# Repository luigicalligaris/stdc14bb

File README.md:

# stdc14bb
A STDC14 breakout board to 100-mil headers, one pair of 100-mil headers being one-to-one to the STDC14 and one being in a single line with additional pins for 3.3V power injection. Licensed under CERN Open Hardware Licence Version 2 - Strongly Reciprocal, see file LICENSE_cern_ohl_s_v2.txt for the full license content.

This board has been designed in KiCAD 7.0.6, a Free and Open Source EDA Software. See the KiCAD site for documentation: https://www.kicad.org/

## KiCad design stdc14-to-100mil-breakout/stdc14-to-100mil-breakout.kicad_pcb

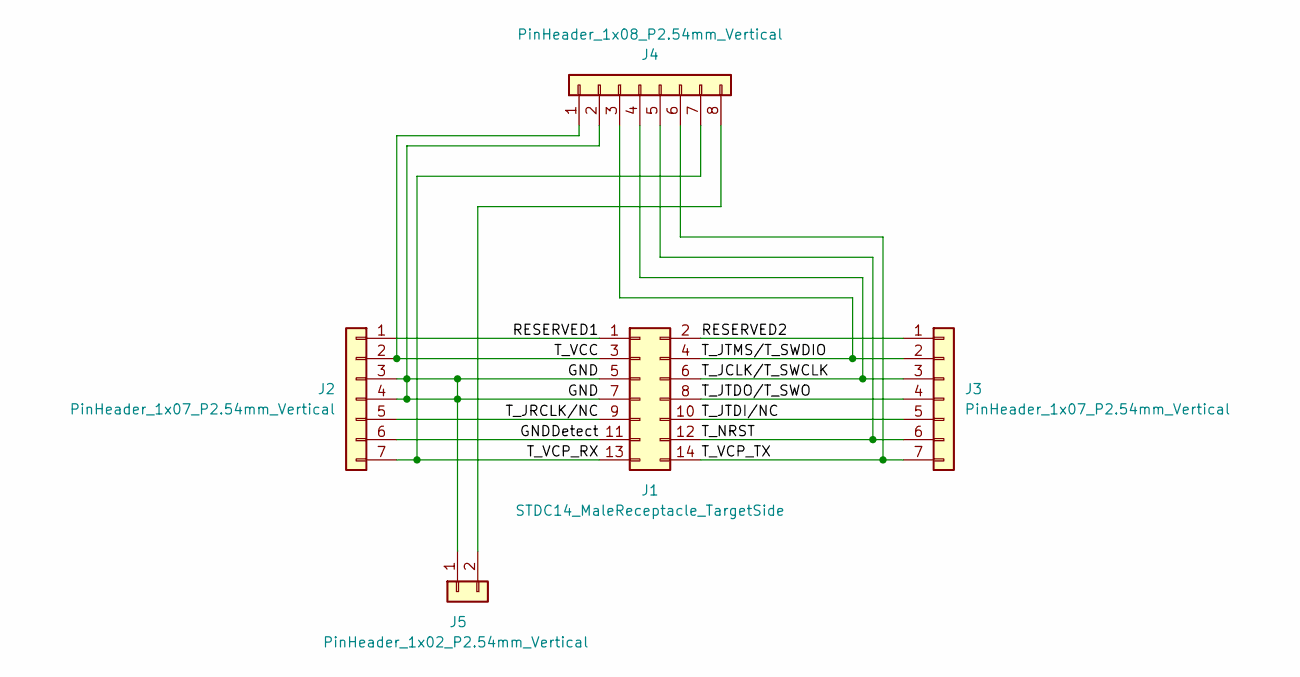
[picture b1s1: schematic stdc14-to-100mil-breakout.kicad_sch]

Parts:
J1: STDC14_MaleReceptacle_TargetSide; IDC-Header_2x07_P1.27mm_Vertical
J2, J3: PinHeader_1x07_P2.54mm_Vertical
J4: PinHeader_1x08_P2.54mm_Vertical
J5: PinHeader_1x02_P2.54mm_Vertical

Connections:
/GND: J1.5 (GND), J1.7, J2.3, J2.4, J4.2, J5.1
/GNDDetect: J1.11 (GNDDetect), J2.6
/RESERVED1: J1.1 (NC), J2.1
/RESERVED2: J1.2 (NC), J3.1
/T_JCLK/T_SWCLK: J1.6 (T_JCLK/T_SWCLK), J3.3, J4.4
/T_JRCLK/NC: J1.9 (T_JRCLK/NC), J2.5
/T_JTDI/NC: J1.10 (T_JTDI/NC), J3.5
/T_JTDO/T_SWO: J1.8 (T_JTDO/T_SWO), J3.4
/T_JTMS/T_SWDIO: J1.4 (T_JTMS/T_SWDIO), J3.2, J4.3
/T_NRST: J1.12 (T_NRST), J3.6, J4.5
/T_VCC: J1.3 (T_VCC), J2.2, J4.1
/T_VCP_RX: J1.13 (T_VCP_RX), J2.7, J4.7
/T_VCP_TX: J1.14 (T_VCP_TX), J3.7, J4.6
unnamed: J4.8, J5.2

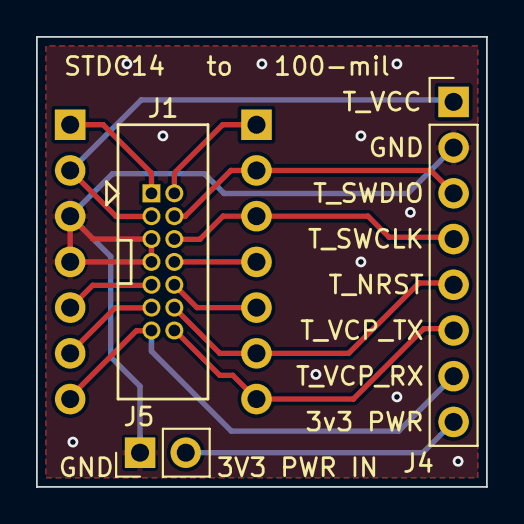
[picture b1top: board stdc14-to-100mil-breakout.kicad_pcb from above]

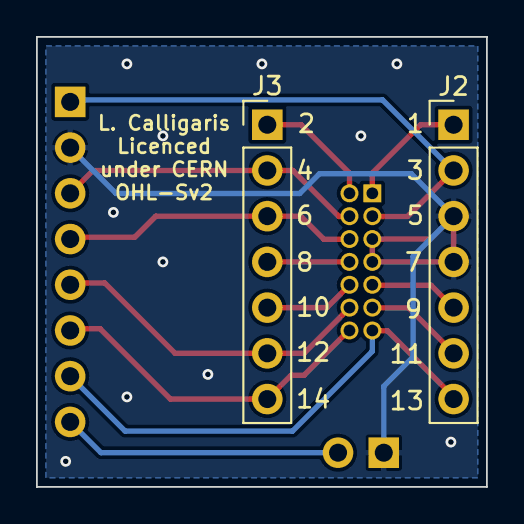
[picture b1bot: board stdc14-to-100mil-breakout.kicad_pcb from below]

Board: 2 copper layers, 25.0 x 25.0 mm, 5 parts (2 on the bottom side), 14 nets.

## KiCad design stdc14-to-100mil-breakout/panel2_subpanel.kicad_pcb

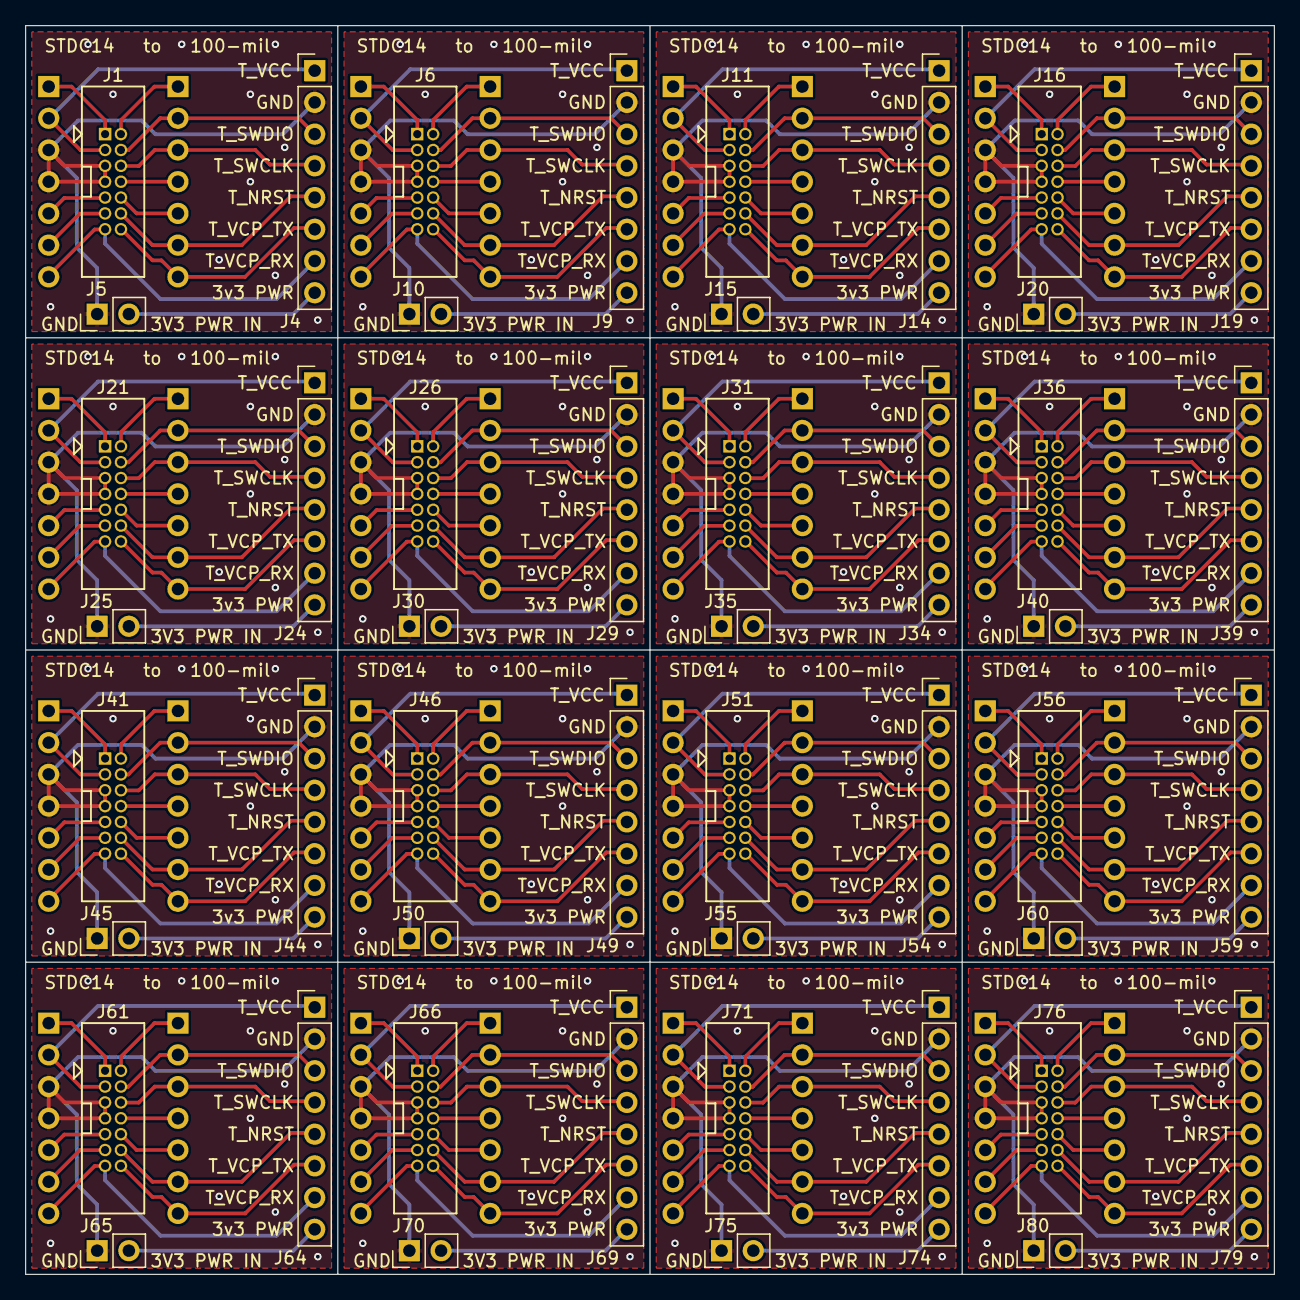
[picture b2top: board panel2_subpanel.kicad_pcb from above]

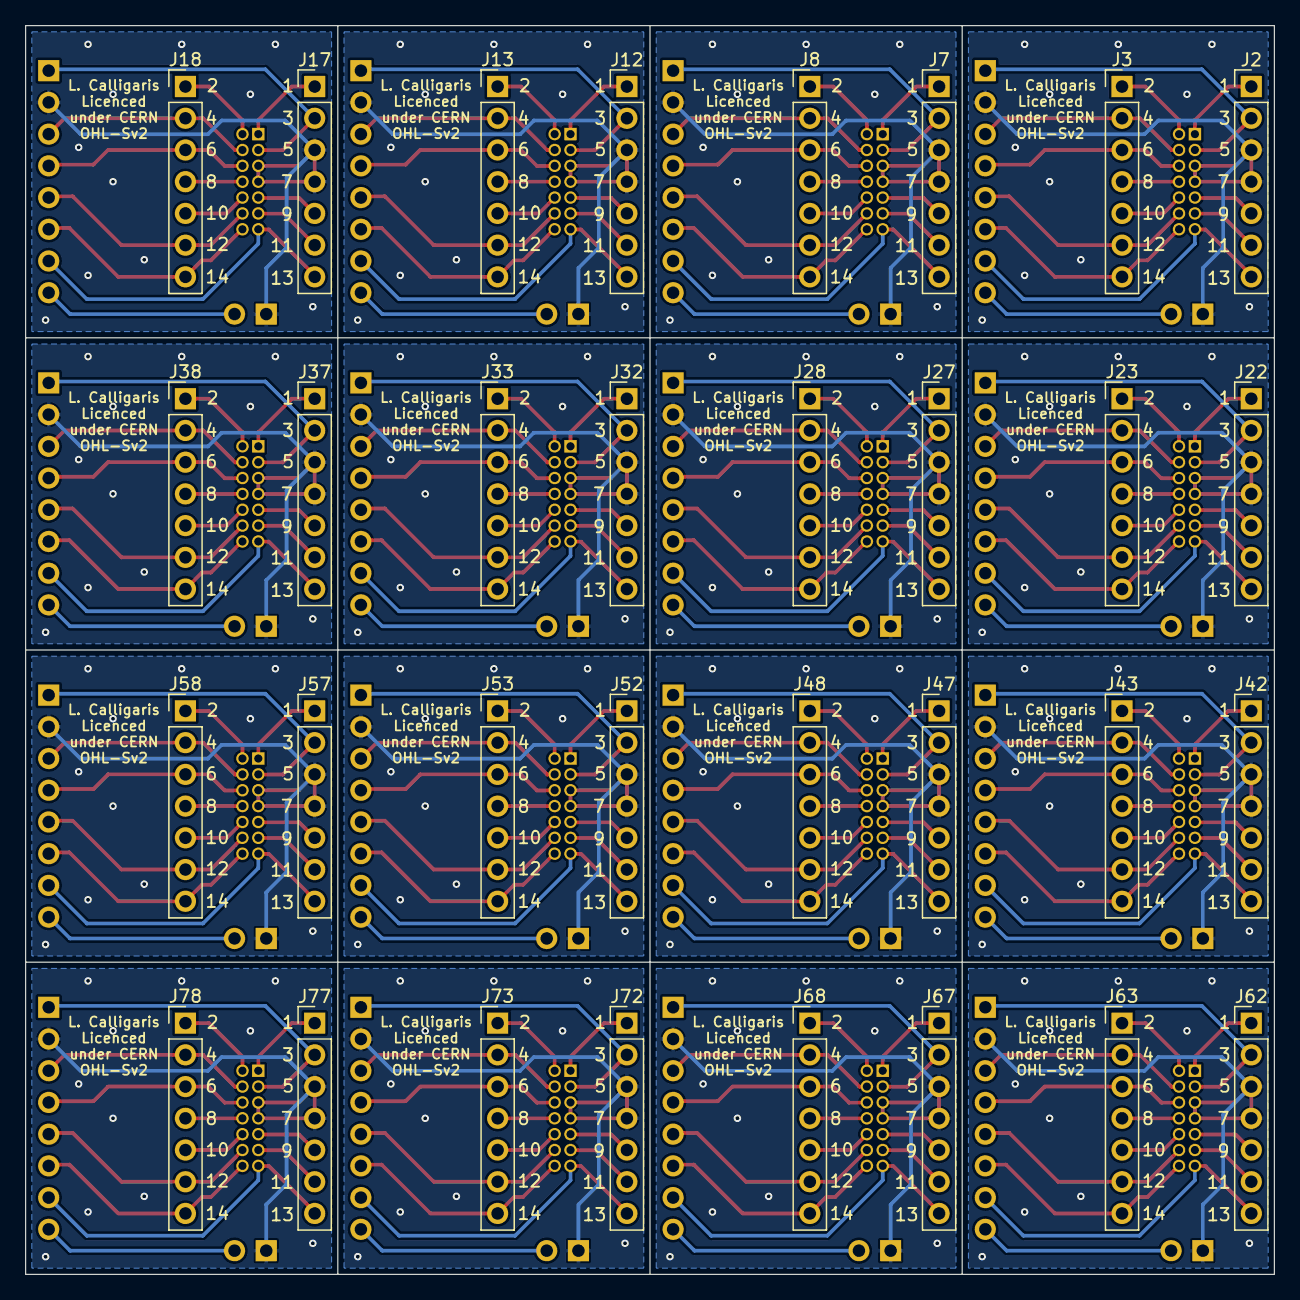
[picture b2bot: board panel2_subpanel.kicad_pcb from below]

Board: 2 copper layers, 100.0 x 100.0 mm, 80 parts (32 on the bottom side), 14 nets.

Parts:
J1, J6, J11, J16, J21, J26, J31, J36, J41, J46, J51, J56, J61, J66, J71, J76: STDC14_MaleReceptacle_TargetSide; IDC-Header_2x07_P1.27mm_Vertical
J2, J3, J7, J8, J12, J13, J17, J18, J22, J23, J27, J28, J32, J33, J37, J38, J42, J43, J47, J48, J52, J53, J57, J58, J62, J63, J67, J68, J72, J73, J77, J78: PinHeader_1x07_P2.54mm_Vertical
J4, J9, J14, J19, J24, J29, J34, J39, J44, J49, J54, J59, J64, J69, J74, J79: PinHeader_1x08_P2.54mm_Vertical
J5, J10, J15, J20, J25, J30, J35, J40, J45, J50, J55, J60, J65, J70, J75, J80: PinHeader_1x02_P2.54mm_Vertical

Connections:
/GND: J1.5 (GND), J1.7, J2.3, J2.4, J4.2, J5.1, J6.5 (GND), J6.7, J7.3, J7.4, J9.2, J10.1, J11.5 (GND), J11.7, J12.3, J12.4, J14.2, J15.1, J16.5 (GND), J16.7, J17.3, J17.4, J19.2, J20.1, J21.5 (GND), J21.7, J22.3, J22.4, J24.2, J25.1, J26.5 (GND), J26.7, J27.3, J27.4, J29.2, J30.1, J31.5 (GND), J31.7, J32.3, J32.4, J34.2, J35.1, J36.5 (GND), J36.7, J37.3, J37.4, J39.2, J40.1, J41.5 (GND), J41.7, J42.3, J42.4, J44.2, J45.1, J46.5 (GND), J46.7, J47.3, J47.4, J49.2, J50.1, J51.5 (GND), J51.7, J52.3, J52.4, J54.2, J55.1, J56.5 (GND), J56.7, J57.3, J57.4, J59.2, J60.1, J61.5 (GND), J61.7, J62.3, J62.4, J64.2, J65.1, J66.5 (GND), J66.7, J67.3, J67.4, J69.2, J70.1, J71.5 (GND), J71.7, J72.3, J72.4, J74.2, J75.1, J76.5 (GND), J76.7, J77.3, J77.4, J79.2, J80.1
/GNDDetect: J1.11 (GNDDetect), J2.6, J6.11 (GNDDetect), J7.6, J11.11 (GNDDetect), J12.6, J16.11 (GNDDetect), J17.6, J21.11 (GNDDetect), J22.6, J26.11 (GNDDetect), J27.6, J31.11 (GNDDetect), J32.6, J36.11 (GNDDetect), J37.6, J41.11 (GNDDetect), J42.6, J46.11 (GNDDetect), J47.6, J51.11 (GNDDetect), J52.6, J56.11 (GNDDetect), J57.6, J61.11 (GNDDetect), J62.6, J66.11 (GNDDetect), J67.6, J71.11 (GNDDetect), J72.6, J76.11 (GNDDetect), J77.6
/RESERVED1: J1.1 (NC), J2.1, J6.1 (NC), J7.1, J11.1 (NC), J12.1, J16.1 (NC), J17.1, J21.1 (NC), J22.1, J26.1 (NC), J27.1, J31.1 (NC), J32.1, J36.1 (NC), J37.1, J41.1 (NC), J42.1, J46.1 (NC), J47.1, J51.1 (NC), J52.1, J56.1 (NC), J57.1, J61.1 (NC), J62.1, J66.1 (NC), J67.1, J71.1 (NC), J72.1, J76.1 (NC), J77.1
/RESERVED2: J1.2 (NC), J3.1, J6.2 (NC), J8.1, J11.2 (NC), J13.1, J16.2 (NC), J18.1, J21.2 (NC), J23.1, J26.2 (NC), J28.1, J31.2 (NC), J33.1, J36.2 (NC), J38.1, J41.2 (NC), J43.1, J46.2 (NC), J48.1, J51.2 (NC), J53.1, J56.2 (NC), J58.1, J61.2 (NC), J63.1, J66.2 (NC), J68.1, J71.2 (NC), J73.1, J76.2 (NC), J78.1
/T_JCLK/T_SWCLK: J1.6 (T_JCLK/T_SWCLK), J3.3, J4.4, J6.6 (T_JCLK/T_SWCLK), J8.3, J9.4, J11.6 (T_JCLK/T_SWCLK), J13.3, J14.4, J16.6 (T_JCLK/T_SWCLK), J18.3, J19.4, J21.6 (T_JCLK/T_SWCLK), J23.3, J24.4, J26.6 (T_JCLK/T_SWCLK), J28.3, J29.4, J31.6 (T_JCLK/T_SWCLK), J33.3, J34.4, J36.6 (T_JCLK/T_SWCLK), J38.3, J39.4, J41.6 (T_JCLK/T_SWCLK), J43.3, J44.4, J46.6 (T_JCLK/T_SWCLK), J48.3, J49.4, J51.6 (T_JCLK/T_SWCLK), J53.3, J54.4, J56.6 (T_JCLK/T_SWCLK), J58.3, J59.4, J61.6 (T_JCLK/T_SWCLK), J63.3, J64.4, J66.6 (T_JCLK/T_SWCLK), J68.3, J69.4, J71.6 (T_JCLK/T_SWCLK), J73.3, J74.4, J76.6 (T_JCLK/T_SWCLK), J78.3, J79.4
/T_JRCLK/NC: J1.9 (T_JRCLK/NC), J2.5, J6.9 (T_JRCLK/NC), J7.5, J11.9 (T_JRCLK/NC), J12.5, J16.9 (T_JRCLK/NC), J17.5, J21.9 (T_JRCLK/NC), J22.5, J26.9 (T_JRCLK/NC), J27.5, J31.9 (T_JRCLK/NC), J32.5, J36.9 (T_JRCLK/NC), J37.5, J41.9 (T_JRCLK/NC), J42.5, J46.9 (T_JRCLK/NC), J47.5, J51.9 (T_JRCLK/NC), J52.5, J56.9 (T_JRCLK/NC), J57.5, J61.9 (T_JRCLK/NC), J62.5, J66.9 (T_JRCLK/NC), J67.5, J71.9 (T_JRCLK/NC), J72.5, J76.9 (T_JRCLK/NC), J77.5
/T_JTDI/NC: J1.10 (T_JTDI/NC), J3.5, J6.10 (T_JTDI/NC), J8.5, J11.10 (T_JTDI/NC), J13.5, J16.10 (T_JTDI/NC), J18.5, J21.10 (T_JTDI/NC), J23.5, J26.10 (T_JTDI/NC), J28.5, J31.10 (T_JTDI/NC), J33.5, J36.10 (T_JTDI/NC), J38.5, J41.10 (T_JTDI/NC), J43.5, J46.10 (T_JTDI/NC), J48.5, J51.10 (T_JTDI/NC), J53.5, J56.10 (T_JTDI/NC), J58.5, J61.10 (T_JTDI/NC), J63.5, J66.10 (T_JTDI/NC), J68.5, J71.10 (T_JTDI/NC), J73.5, J76.10 (T_JTDI/NC), J78.5
/T_JTDO/T_SWO: J1.8 (T_JTDO/T_SWO), J3.4, J6.8 (T_JTDO/T_SWO), J8.4, J11.8 (T_JTDO/T_SWO), J13.4, J16.8 (T_JTDO/T_SWO), J18.4, J21.8 (T_JTDO/T_SWO), J23.4, J26.8 (T_JTDO/T_SWO), J28.4, J31.8 (T_JTDO/T_SWO), J33.4, J36.8 (T_JTDO/T_SWO), J38.4, J41.8 (T_JTDO/T_SWO), J43.4, J46.8 (T_JTDO/T_SWO), J48.4, J51.8 (T_JTDO/T_SWO), J53.4, J56.8 (T_JTDO/T_SWO), J58.4, J61.8 (T_JTDO/T_SWO), J63.4, J66.8 (T_JTDO/T_SWO), J68.4, J71.8 (T_JTDO/T_SWO), J73.4, J76.8 (T_JTDO/T_SWO), J78.4
/T_JTMS/T_SWDIO: J1.4 (T_JTMS/T_SWDIO), J3.2, J4.3, J6.4 (T_JTMS/T_SWDIO), J8.2, J9.3, J11.4 (T_JTMS/T_SWDIO), J13.2, J14.3, J16.4 (T_JTMS/T_SWDIO), J18.2, J19.3, J21.4 (T_JTMS/T_SWDIO), J23.2, J24.3, J26.4 (T_JTMS/T_SWDIO), J28.2, J29.3, J31.4 (T_JTMS/T_SWDIO), J33.2, J34.3, J36.4 (T_JTMS/T_SWDIO), J38.2, J39.3, J41.4 (T_JTMS/T_SWDIO), J43.2, J44.3, J46.4 (T_JTMS/T_SWDIO), J48.2, J49.3, J51.4 (T_JTMS/T_SWDIO), J53.2, J54.3, J56.4 (T_JTMS/T_SWDIO), J58.2, J59.3, J61.4 (T_JTMS/T_SWDIO), J63.2, J64.3, J66.4 (T_JTMS/T_SWDIO), J68.2, J69.3, J71.4 (T_JTMS/T_SWDIO), J73.2, J74.3, J76.4 (T_JTMS/T_SWDIO), J78.2, J79.3
/T_NRST: J1.12 (T_NRST), J3.6, J4.5, J6.12 (T_NRST), J8.6, J9.5, J11.12 (T_NRST), J13.6, J14.5, J16.12 (T_NRST), J18.6, J19.5, J21.12 (T_NRST), J23.6, J24.5, J26.12 (T_NRST), J28.6, J29.5, J31.12 (T_NRST), J33.6, J34.5, J36.12 (T_NRST), J38.6, J39.5, J41.12 (T_NRST), J43.6, J44.5, J46.12 (T_NRST), J48.6, J49.5, J51.12 (T_NRST), J53.6, J54.5, J56.12 (T_NRST), J58.6, J59.5, J61.12 (T_NRST), J63.6, J64.5, J66.12 (T_NRST), J68.6, J69.5, J71.12 (T_NRST), J73.6, J74.5, J76.12 (T_NRST), J78.6, J79.5
/T_VCC: J1.3 (T_VCC), J2.2, J4.1, J6.3 (T_VCC), J7.2, J9.1, J11.3 (T_VCC), J12.2, J14.1, J16.3 (T_VCC), J17.2, J19.1, J21.3 (T_VCC), J22.2, J24.1, J26.3 (T_VCC), J27.2, J29.1, J31.3 (T_VCC), J32.2, J34.1, J36.3 (T_VCC), J37.2, J39.1, J41.3 (T_VCC), J42.2, J44.1, J46.3 (T_VCC), J47.2, J49.1, J51.3 (T_VCC), J52.2, J54.1, J56.3 (T_VCC), J57.2, J59.1, J61.3 (T_VCC), J62.2, J64.1, J66.3 (T_VCC), J67.2, J69.1, J71.3 (T_VCC), J72.2, J74.1, J76.3 (T_VCC), J77.2, J79.1
/T_VCP_RX: J1.13 (T_VCP_RX), J2.7, J4.7, J6.13 (T_VCP_RX), J7.7, J9.7, J11.13 (T_VCP_RX), J12.7, J14.7, J16.13 (T_VCP_RX), J17.7, J19.7, J21.13 (T_VCP_RX), J22.7, J24.7, J26.13 (T_VCP_RX), J27.7, J29.7, J31.13 (T_VCP_RX), J32.7, J34.7, J36.13 (T_VCP_RX), J37.7, J39.7, J41.13 (T_VCP_RX), J42.7, J44.7, J46.13 (T_VCP_RX), J47.7, J49.7, J51.13 (T_VCP_RX), J52.7, J54.7, J56.13 (T_VCP_RX), J57.7, J59.7, J61.13 (T_VCP_RX), J62.7, J64.7, J66.13 (T_VCP_RX), J67.7, J69.7, J71.13 (T_VCP_RX), J72.7, J74.7, J76.13 (T_VCP_RX), J77.7, J79.7
/T_VCP_TX: J1.14 (T_VCP_TX), J3.7, J4.6, J6.14 (T_VCP_TX), J8.7, J9.6, J11.14 (T_VCP_TX), J13.7, J14.6, J16.14 (T_VCP_TX), J18.7, J19.6, J21.14 (T_VCP_TX), J23.7, J24.6, J26.14 (T_VCP_TX), J28.7, J29.6, J31.14 (T_VCP_TX), J33.7, J34.6, J36.14 (T_VCP_TX), J38.7, J39.6, J41.14 (T_VCP_TX), J43.7, J44.6, J46.14 (T_VCP_TX), J48.7, J49.6, J51.14 (T_VCP_TX), J53.7, J54.6, J56.14 (T_VCP_TX), J58.7, J59.6, J61.14 (T_VCP_TX), J63.7, J64.6, J66.14 (T_VCP_TX), J68.7, J69.6, J71.14 (T_VCP_TX), J73.7, J74.6, J76.14 (T_VCP_TX), J78.7, J79.6
unnamed: J4.8, J5.2, J9.8, J10.2, J14.8, J15.2, J19.8, J20.2, J24.8, J25.2, J29.8, J30.2, J34.8, J35.2, J39.8, J40.2, J44.8, J45.2, J49.8, J50.2, J54.8, J55.2, J59.8, J60.2, J64.8, J65.2, J69.8, J70.2, J74.8, J75.2, J79.8, J80.2

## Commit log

2024-05-15 Put in version control v1.1. This version adds the OHW logo and mention of the license on the silkscreen
2024-05-15 Update README.md to specify license file
2025-04-29 Add part numbers for stdc connector
